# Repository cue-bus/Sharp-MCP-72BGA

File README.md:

# Sharp-MCP-72BGA
Breakout adapter for Sharp MCP chips in BGA72 package

Most Sharp MCP flash chips use the same main pinout for the the flash interface, but provisions have been made on the adapter board to allow for changes if necessary.
1. Pin 47 can either be NC, CE2, or VCCQ depending on the chip. It is prewired to ball H3, but if necessary, cut the trace where indicated and wire a jumper wire from Pin 47 to wherever it's needed. 
2. A10 and H10 have functions on some chips, so they are broken out to allow for easy access if necessary. Otherwise, these can be left as NC. Ball H10 is CE2 on a few single-die Sharp chips, but so far every MCP has featured CE2 on ball H3.
3. Chips under 32mbits use a slightly different DIP pinout that this adapter maps to the BGAs. For chips of this size, either swap pins 9 and 15, or simply read the chip as 64mbit and truncate the file to the necessary size.

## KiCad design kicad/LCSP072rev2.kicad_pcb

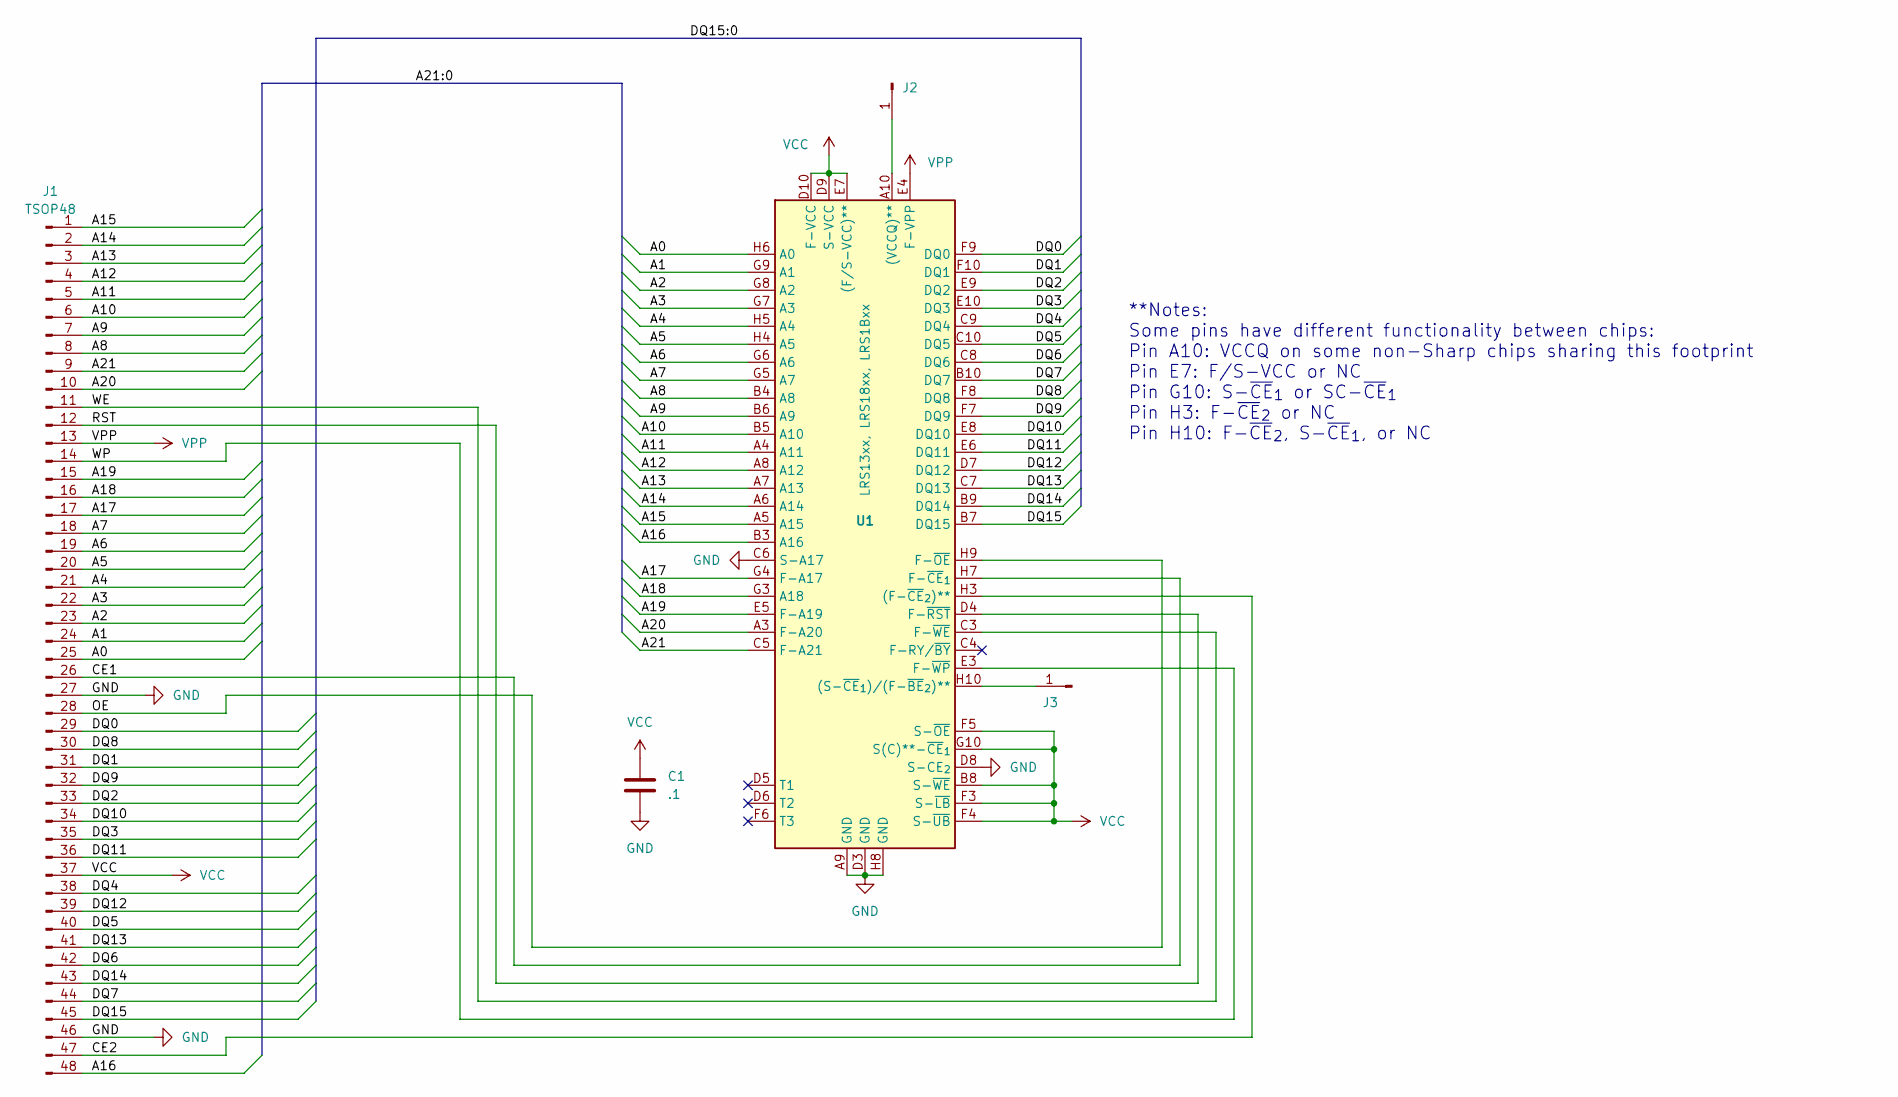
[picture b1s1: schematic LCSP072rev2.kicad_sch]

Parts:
C1: .1; C_0805_2012Metric_Pad1.18x1.45mm_HandSolder
J1: TSOP48; DIP-48_W15.24mm_Socket_LongPads
J2: A10; SolderWire-0.127sqmm_1x01_D0.48mm_OD1mm
J3: H10; SolderWire-0.127sqmm_1x01_D0.48mm_OD1mm
U1: LRS13xx, LRS18xx, LRS1Bxx; LCSP072

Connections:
/A0: J1.25, U1.H6 (A0)
/A1: J1.24, U1.G9 (A1)
/A2: J1.23, U1.G8 (A2)
/A3: J1.22, U1.G7 (A3)
/A4: J1.21, U1.H5 (A4)
/A5: J1.20, U1.H4 (A5)
/A6: J1.19, U1.G6 (A6)
/A7: J1.18, U1.G5 (A7)
/A8: J1.8, U1.B4 (A8)
/A9: J1.7, U1.B6 (A9)
/A10: J1.6, U1.B5 (A10)
/A11: J1.5, U1.A4 (A11)
/A12: J1.4, U1.A8 (A12)
/A13: J1.3, U1.A7 (A13)
/A14: J1.2, U1.A6 (A14)
/A15: J1.1, U1.A5 (A15)
/A16: J1.48, U1.B3 (A16)
/A17: J1.17, U1.G4 (F-A17)
/A18: J1.16, U1.G3 (A18)
/A19: J1.15, U1.E5 (F-A19)
/A20: J1.10, U1.A3 (F-A20)
/A21: J1.9, U1.C5 (F-A21)
/CE1: J1.26, U1.H7 (F-~CE_{1})
/CE2: J1.47, U1.H3 ((F-~CE_{2})**)
/DQ0: J1.29, U1.F9 (DQ0)
/DQ1: J1.31, U1.F10 (DQ1)
/DQ2: J1.33, U1.E9 (DQ2)
/DQ3: J1.35, U1.E10 (DQ3)
/DQ4: J1.38, U1.C9 (DQ4)
/DQ5: J1.40, U1.C10 (DQ5)
/DQ6: J1.42, U1.C8 (DQ6)
/DQ7: J1.44, U1.B10 (DQ7)
/DQ8: J1.30, U1.F8 (DQ8)
/DQ9: J1.32, U1.F7 (DQ9)
/DQ10: J1.34, U1.E8 (DQ10)
/DQ11: J1.36, U1.E6 (DQ11)
/DQ12: J1.39, U1.D7 (DQ12)
/DQ13: J1.41, U1.C7 (DQ13)
/DQ14: J1.43, U1.B9 (DQ14)
/DQ15: J1.45, U1.B7 (DQ15)
/OE: J1.28, U1.H9 (F-~OE)
/RST: J1.12, U1.D4 (F-~RST)
/WE: J1.11, U1.C3 (F-~WE)
/WP: J1.14, U1.E3 (F-~WP)
GND: C1.2, J1.27, J1.46, U1.A9 (GND), U1.C6 (S-A17), U1.D3 (GND), U1.D8 (S-CE_{2}), U1.H8 (GND)
unnamed: J2.1, U1.A10 ((VCCQ)**)
unnamed: J3.1, U1.H10 ((S-~CE_{1})/(F-~BE_{2})**)
VCC: C1.1, J1.37, U1.B8 (S-~WE), U1.D9 (S-VCC), U1.D10 (F-VCC), U1.E7 ((F/S-VCC)**), U1.F3 (S-~LB), U1.F4 (S-~UB), U1.F5 (S-~OE), U1.G10 (S(C)**-~CE_{1})
VPP: J1.13, U1.E4 (F-VPP)

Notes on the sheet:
**Notes: Some pins have different functionality between chips: Pin A10: VCCQ on some non-Sharp chips sharing this footprint Pin E7: F/S-VCC or NC Pin G10: S-~{CE}_{1} or SC-~{CE}_{1} Pin H3: F-~{CE}_{2} or NC Pin H10: F-~{CE}_{2}, S-~{CE}_{1}, or NC

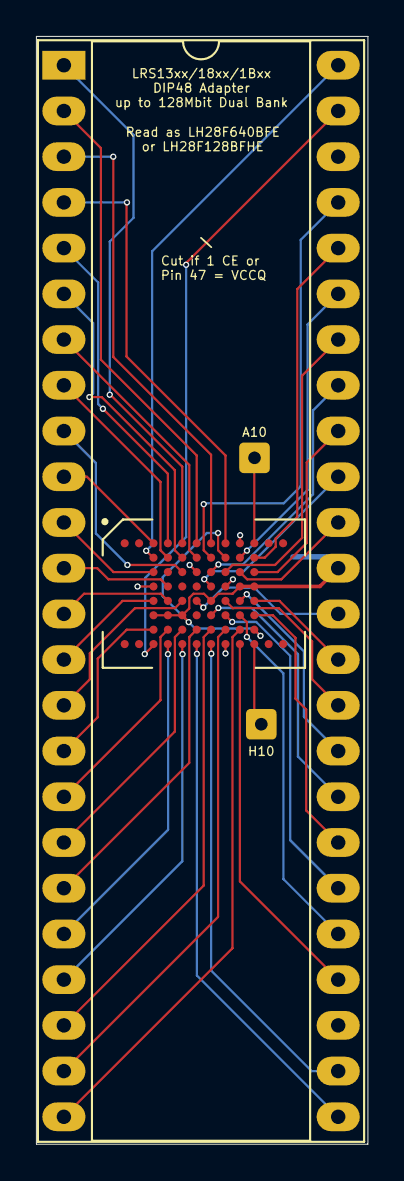
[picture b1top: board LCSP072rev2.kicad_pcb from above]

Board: 2 copper layers, 18.4 x 61.5 mm, 5 parts (1 on the bottom side), 49 nets.

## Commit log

2024-11-10 Added files
